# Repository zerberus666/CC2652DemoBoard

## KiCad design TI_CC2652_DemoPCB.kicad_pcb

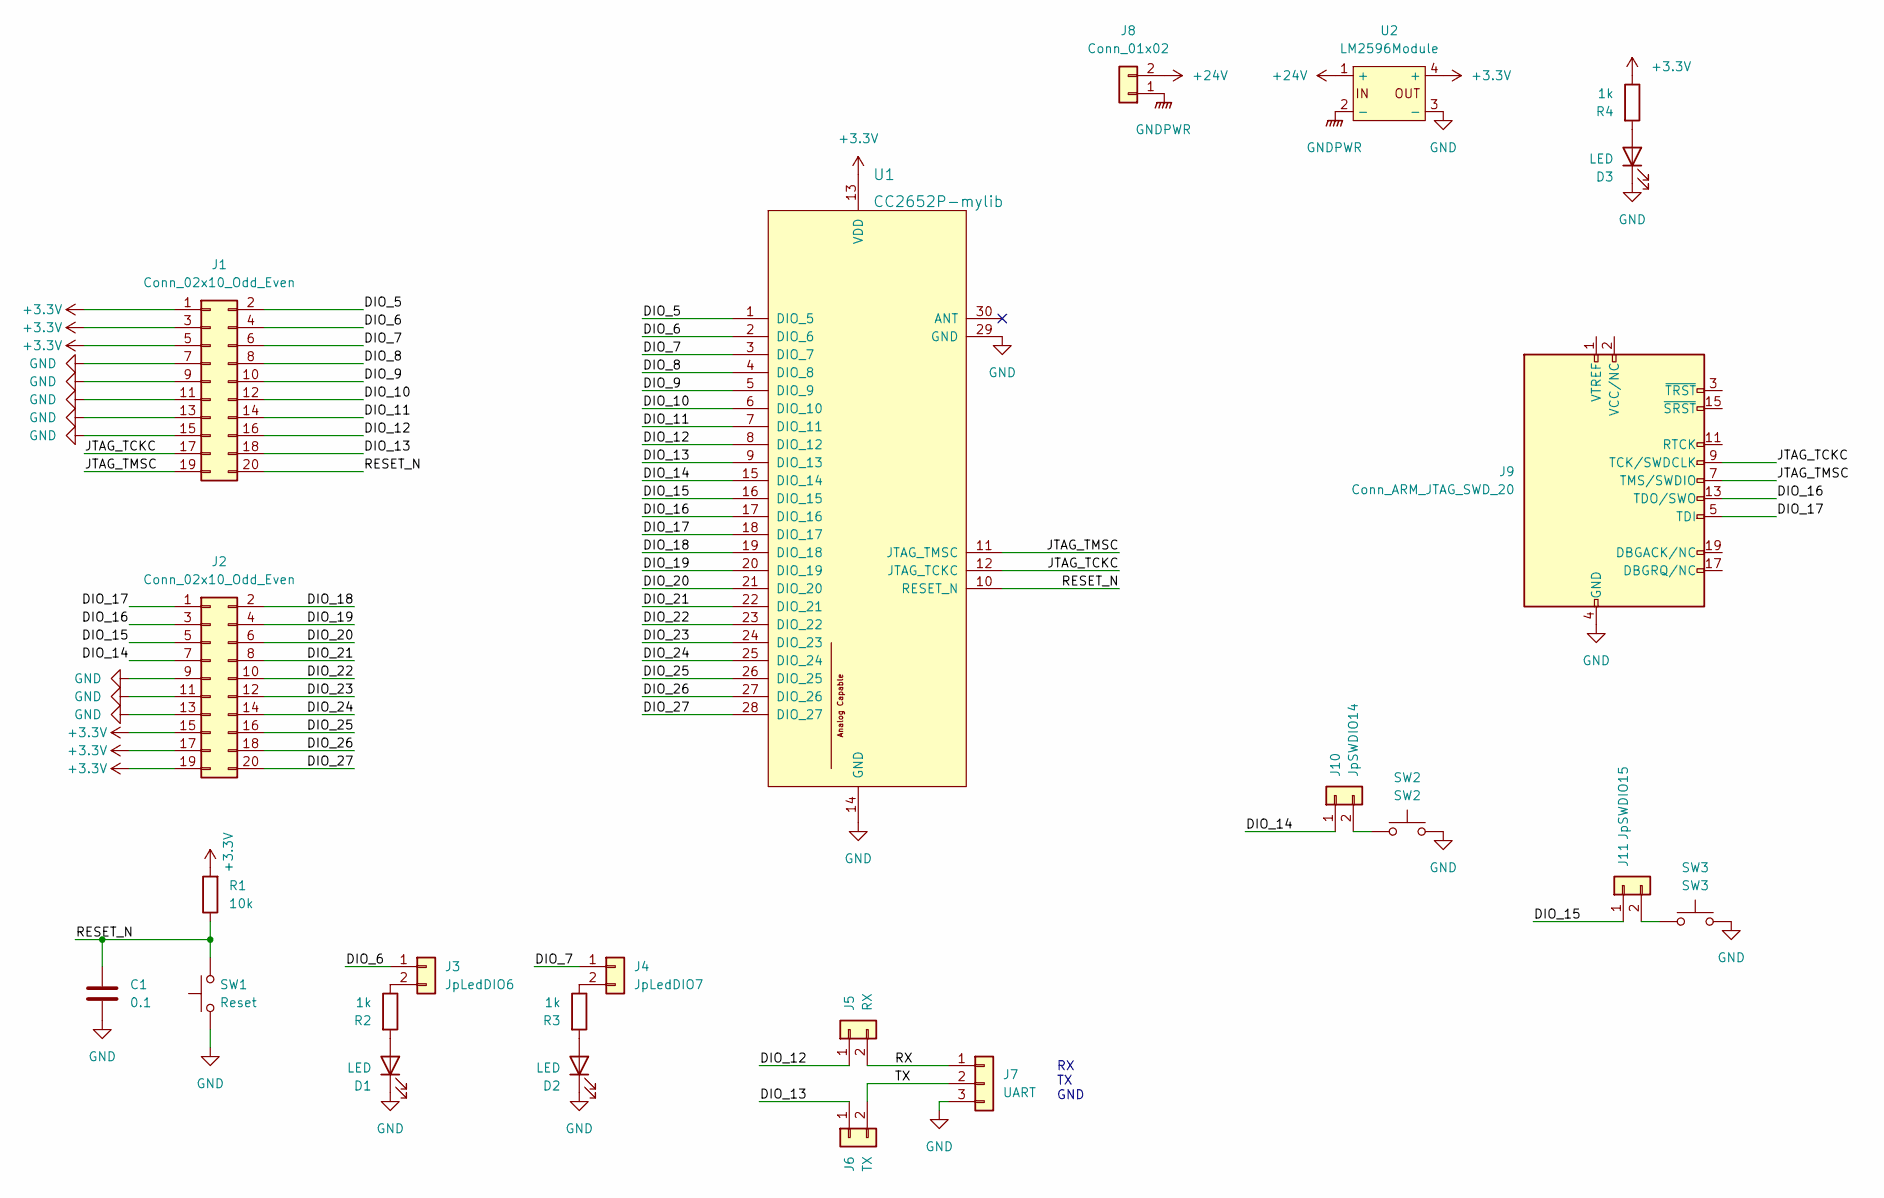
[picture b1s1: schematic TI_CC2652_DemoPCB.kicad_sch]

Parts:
C1: 0.1; C_0805_2012Metric
D1, D2, D3: LED; LED_0805_2012Metric
J1, J2: Conn_02x10_Odd_Even; PinHeader_2x10_P2.54mm_Vertical
J3: JpLedDIO6; PinHeader_1x02_P2.54mm_Vertical
J4: JpLedDIO7; PinHeader_1x02_P2.54mm_Vertical
J5: RX; PinHeader_1x02_P2.54mm_Vertical
J6: TX; PinHeader_1x02_P2.54mm_Vertical
J7: UART; PinHeader_1x03_P2.54mm_Vertical
J8: Conn_01x02; DG142V-5.08-2
J9: Conn_ARM_JTAG_SWD_20; PinHeader_2x10_P2.54mm_Vertical
J10: JpSWDIO14; PinHeader_1x02_P2.54mm_Vertical
J11: JpSWDIO15; PinHeader_1x02_P2.54mm_Vertical
R1: 10k; R_1206_3216Metric
R2, R3, R4: 1k; R_1206_3216Metric
SW1: Reset; SW_PUSH_6mm_H4.3mm
SW2: SW2; SW_PUSH_6mm_H4.3mm
SW3: SW3; SW_PUSH_6mm_H4.3mm
U1: CC2652P-mylib; RF-BM-2652P2; MPN RF-BM-2652P2
U2: LM2596Module

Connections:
+3V3: J1.1, J1.3, J1.5, J2.15, J2.17, J2.19, R1.2, R4.1, U1.13 (VDD), U2.4 (+)
+24V: J8.2, U2.1 (+)
/DIO_5: J1.2, U1.1 (DIO_5)
/DIO_6: J1.4, J3.1, U1.2 (DIO_6)
/DIO_7: J1.6, J4.1, U1.3 (DIO_7)
/DIO_8: J1.8, U1.4 (DIO_8)
/DIO_9: J1.10, U1.5 (DIO_9)
/DIO_10: J1.12, U1.6 (DIO_10)
/DIO_11: J1.14, U1.7 (DIO_11)
/DIO_12: J1.16, J5.1, U1.8 (DIO_12)
/DIO_13: J1.18, J6.1, U1.9 (DIO_13)
/DIO_14: J2.7, J10.1, U1.15 (DIO_14)
/DIO_15: J2.5, J11.1, U1.16 (DIO_15)
/DIO_16: J2.3, J9.13 (TDO/SWO), U1.17 (DIO_16)
/DIO_17: J2.1, J9.5 (TDI), U1.18 (DIO_17)
/DIO_18: J2.2, U1.19 (DIO_18)
/DIO_19: J2.4, U1.20 (DIO_19)
/DIO_20: J2.6, U1.21 (DIO_20)
/DIO_21: J2.8, U1.22 (DIO_21)
/DIO_22: J2.10, U1.23 (DIO_22)
/DIO_23: J2.12, U1.24 (DIO_23)
/DIO_24: J2.14, U1.25 (DIO_24)
/DIO_25: J2.16, U1.26 (DIO_25)
/DIO_26: J2.18, U1.27 (DIO_26)
/DIO_27: J2.20, U1.28 (DIO_27)
/JTAG_TCKC: J1.17, J9.9 (TCK/SWDCLK), U1.12 (JTAG_TCKC)
/JTAG_TMSC: J1.19, J9.7 (TMS/SWDIO), U1.11 (JTAG_TMSC)
/RESET_N: C1.1, J1.20, R1.1, SW1.2, U1.10 (RESET_N)
/RX: J5.2, J7.1
/TX: J6.2, J7.2
GND: C1.2, D1.1 (K), D2.1 (K), D3.1 (K), J1.7, J1.9, J1.11, J1.13, J1.15, J2.9, J2.11, J2.13, J7.3, J9.4 (GND), J9.6 (GND), J9.8 (GND), J9.10 (GND), J9.12 (GND), J9.14 (GND), J9.16 (GND), J9.18 (GND), J9.20 (GND), SW1.1, SW2.2, SW3.2, U1.14 (GND), U1.29 (GND), U2.3 (-)
GNDPWR: J8.1, U2.2 (-)
unnamed: D1.2 (A), R2.2
unnamed: D2.2 (A), R3.2
unnamed: D3.2 (A), R4.2
unnamed: J3.2, R2.1
unnamed: J4.2, R3.1
unnamed: J10.2, SW2.1
unnamed: J11.2, SW3.1

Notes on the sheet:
RX TX GND

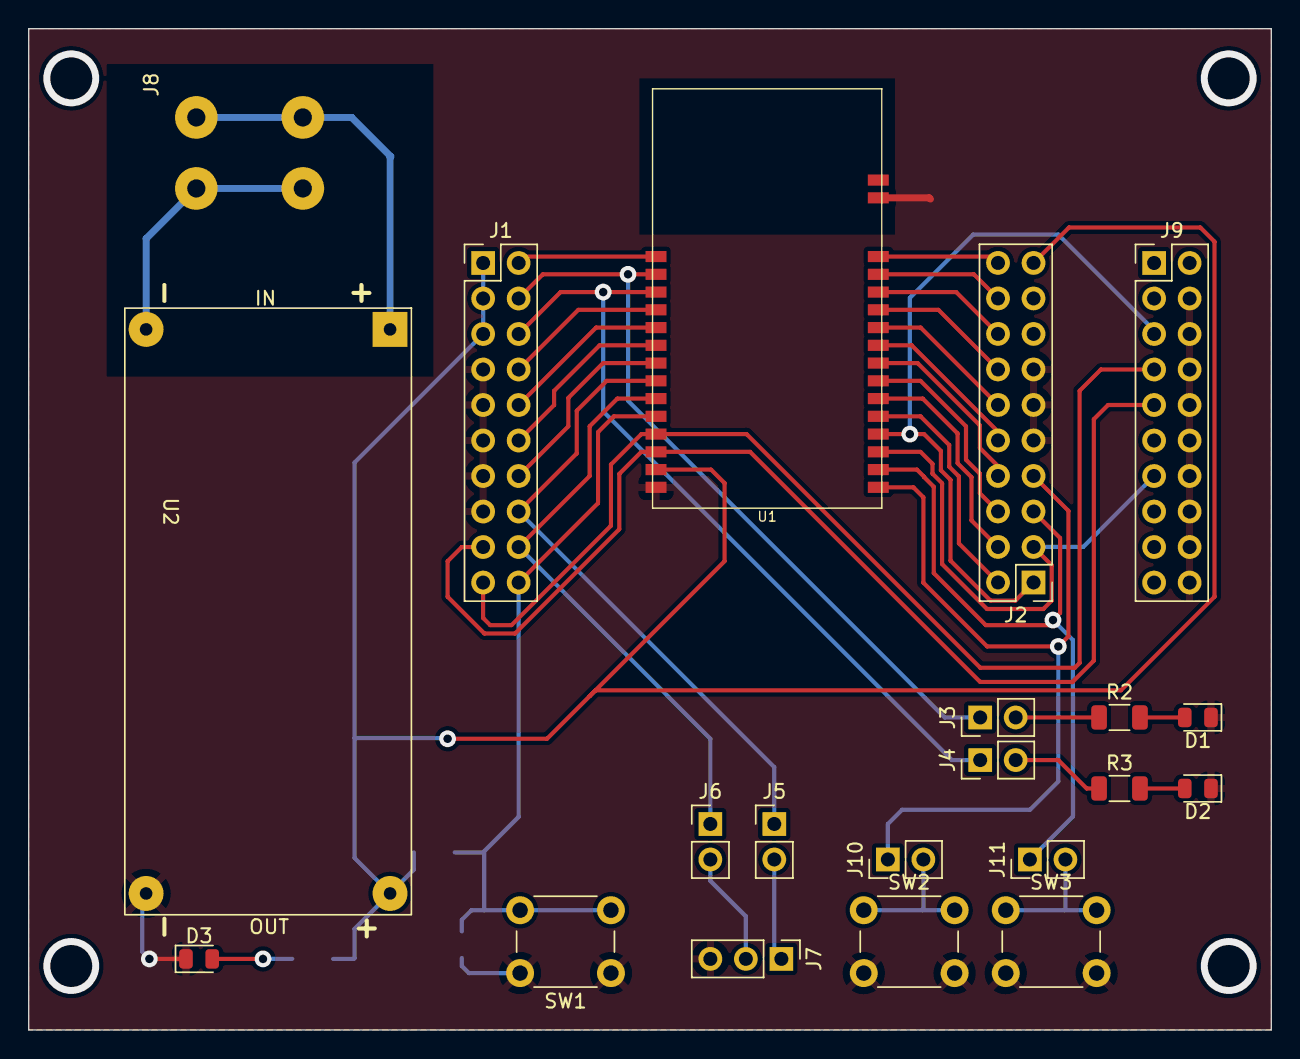
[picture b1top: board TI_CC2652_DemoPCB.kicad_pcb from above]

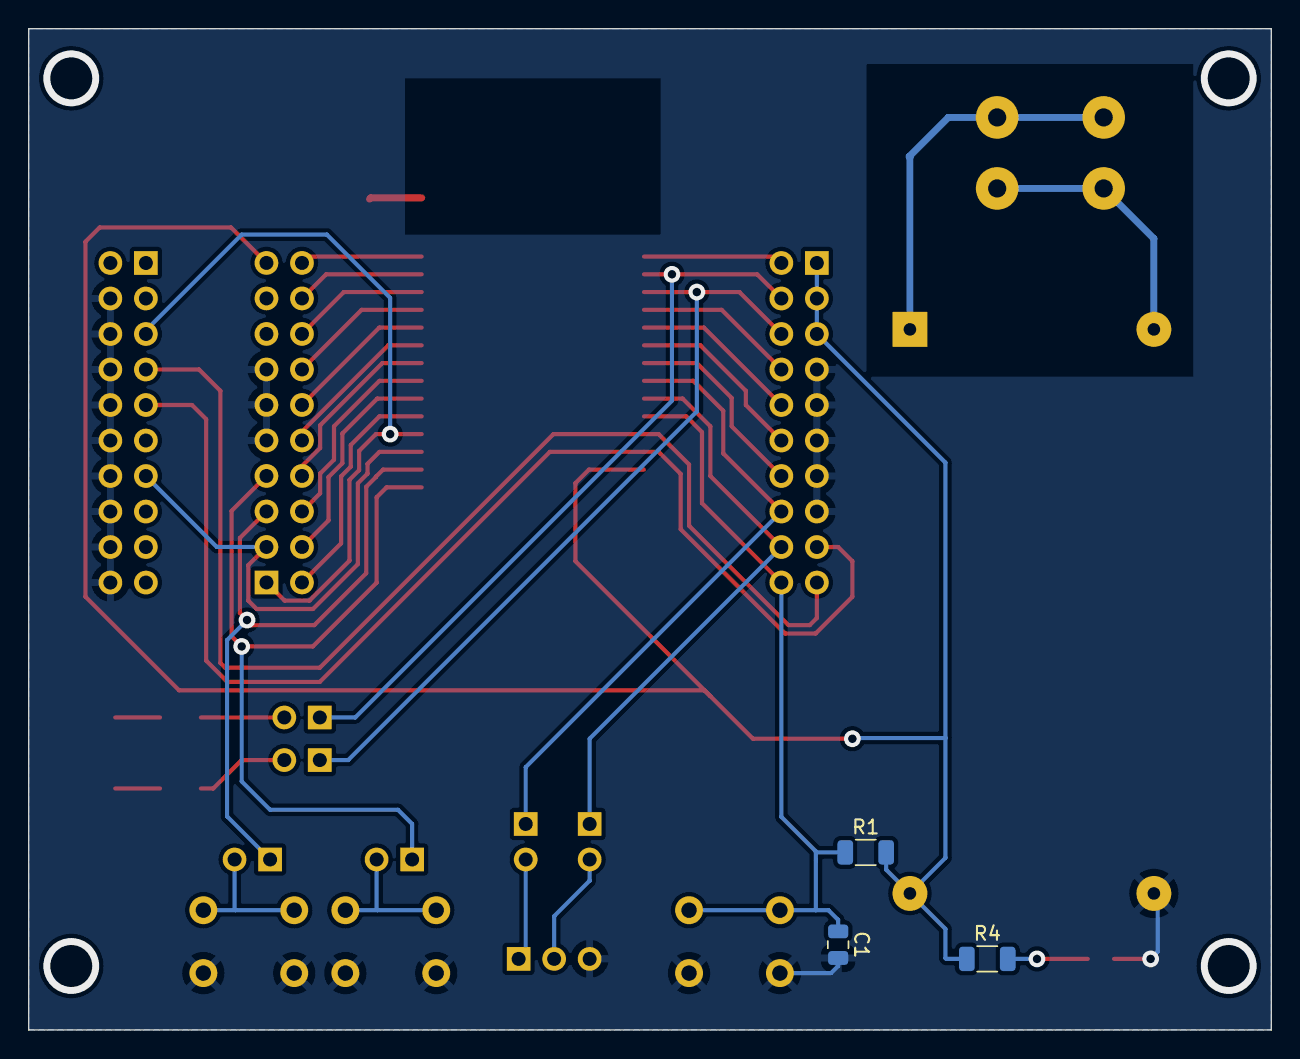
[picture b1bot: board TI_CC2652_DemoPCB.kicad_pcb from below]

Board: 2 copper layers, 88.9 x 71.6 mm, 24 parts (3 on the bottom side), 39 nets.

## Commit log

2022-02-22 initial
2022-02-22 LEDs Added
2022-02-28 PCB added
2022-03-05 сс2652 module moved to top side
